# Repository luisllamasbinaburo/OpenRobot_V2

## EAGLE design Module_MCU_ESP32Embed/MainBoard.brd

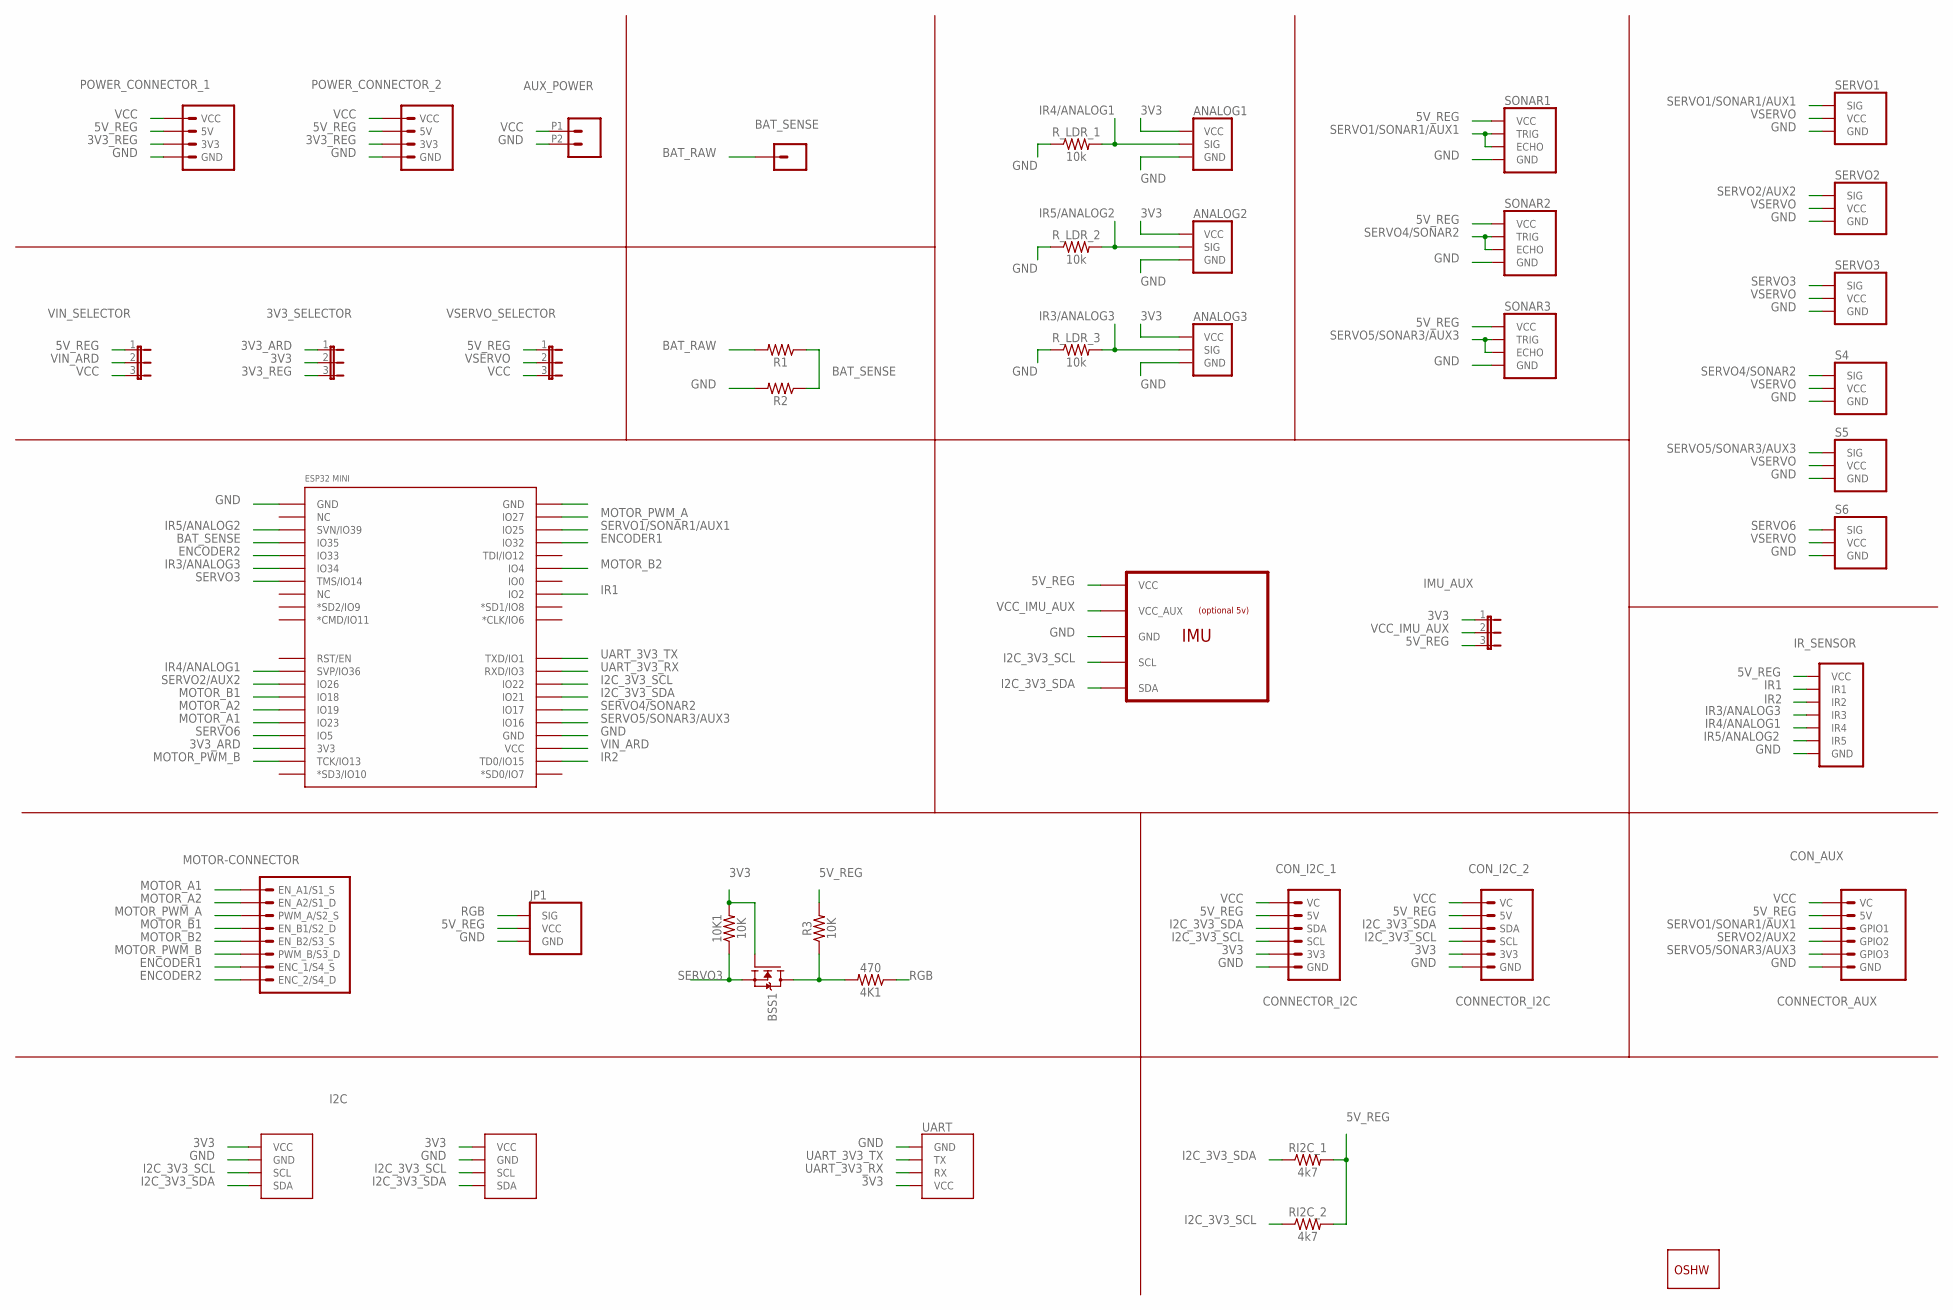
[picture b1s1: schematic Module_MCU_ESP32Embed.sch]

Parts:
3V3_SELECTOR: JUMPER_3
4K1: 470; 0805
10K1: 10K; 0805
ANALOG1, ANALOG2, ANALOG3: LDR/OCT; LDR
AUX_POWER: CONN_022.54MM_SCREWTERM; 1X02_2.54_SCREWTERM
BAT_SENSE: CONN_01; 1X01
BSS1: MOSFET-N-SOT23; SOT23
CON_AUX: CONNECTOR_AUX
CON_I2C_1, CON_I2C_2: CONNECTOR_I2C
GOLD_ORB_SM1: OSHWLOGO_GOLD_ORB_MED; OSHW1
I2C_1: I2C; I2C_VCC_GND_SCL_SDA
I2C_2: GENERIC_I2CVCC_GND_SCL_SDA; I2C_VCC_GND_SCL_SDA
IMU_AUX: JUMPER_3
IR_SENSOR: IR-5/OCT; IR-5
JP1: SERVOSERVO; SERVO
MOTOR_CONNECTOR: MOTOR-CONNECTOR
POWER_CONNECTOR_1, POWER_CONNECTOR_2: POWER-CONNECTOR
R1, R2: 1206
R3: 10K; 0805
RI2C_1, RI2C_2: 4k7; 1206
R_LDR_1, R_LDR_2, R_LDR_3: 10k; 1206
S4, S5, S6: SERVOSERVO; SERVO
SERVO1, SERVO2, SERVO3: SERVOSERVO; SERVO
SONAR1, SONAR2, SONAR3: ULTRASONIC/OCT; ULTRASONIC
U1: IMU_6/9/10DOFMPU6050; IMU_6/9/10DOF
U$5: ESP32-WEMOS
UART: UART; GENERIC_UART
VIN_SELECTOR: JUMPER_3
VSERVO_SELECTOR: JUMPER_3

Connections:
3V3_ARD: 3V3_SELECTOR.1, U$5.3V3
3V3_REG: 3V3_SELECTOR.3, POWER_CONNECTOR_1.3V3, POWER_CONNECTOR_2.3V3
BAT_RAW: BAT_SENSE.1, R1.2
BAT_SENSE: R1.1, R2.1, U$5.IO35
ENCODER1: MOTOR_CONNECTOR.ENC_1/S4_S, U$5.IO32
ENCODER2: MOTOR_CONNECTOR.ENC_2/S4_D, U$5.IO33
GND: ANALOG1.GND, ANALOG2.GND, ANALOG3.GND, AUX_POWER.P2 (2), CON_AUX.GND, CON_I2C_1.GND, CON_I2C_2.GND, I2C_1.GND, I2C_2.GND, IR_SENSOR.GND, JP1.GND, POWER_CONNECTOR_1.GND, POWER_CONNECTOR_2.GND, R2.2, R_LDR_1.1, R_LDR_2.1, R_LDR_3.1, S4.GND, S5.GND, S6.GND, SERVO1.GND, SERVO2.GND, SERVO3.GND, SONAR1.GND, SONAR2.GND, SONAR3.GND, U1.GND, U$5.GND@1 (GND), U$5.GND@3 (GND), UART.GND
I2C_3V3_SCL: CON_I2C_1.SCL, CON_I2C_2.SCL, I2C_1.SCL, I2C_2.SCL, RI2C_2.1, U1.SCL, U$5.IO22
I2C_3V3_SDA: CON_I2C_1.SDA, CON_I2C_2.SDA, I2C_1.SDA, I2C_2.SDA, RI2C_1.1, U1.SDA, U$5.IO21
IR1: IR_SENSOR.1 (IR1), U$5.IO2
IR2: IR_SENSOR.2 (IR2), U$5.TD0/IO15
IR3/ANALOG3: ANALOG3.SIG, IR_SENSOR.3 (IR3), R_LDR_3.2, U$5.IO34
IR4/ANALOG1: ANALOG1.SIG, IR_SENSOR.4 (IR4), R_LDR_1.2, U$5.SVP/IO36
IR5/ANALOG2: ANALOG2.SIG, IR_SENSOR.5 (IR5), R_LDR_2.2, U$5.SVN/IO39
MOTOR_A1: MOTOR_CONNECTOR.EN_A1/S1_S, U$5.IO23
MOTOR_A2: MOTOR_CONNECTOR.EN_A2/S1_D, U$5.IO19
MOTOR_B1: MOTOR_CONNECTOR.EN_B1/S2_D, U$5.IO18
MOTOR_B2: MOTOR_CONNECTOR.EN_B2/S3_S, U$5.IO4
MOTOR_PWM_A: MOTOR_CONNECTOR.PWM_A/S2_S, U$5.IO27
MOTOR_PWM_B: MOTOR_CONNECTOR.PWM_B/S3_D, U$5.TCK/IO13
unnamed: 4K1.2, BSS1.3 (D), R3.1
RGB: 4K1.1, JP1.SIG
SERVO1/SONAR1/AUX1: CON_AUX.GPIO1, SERVO1.SIG, SONAR1.ECHO, SONAR1.TRIG, U$5.IO25
SERVO2/AUX2: CON_AUX.GPIO2, SERVO2.SIG, U$5.IO26
SERVO3: 10K1.1, BSS1.2 (S), SERVO3.SIG, U$5.TMS/IO14
SERVO4/SONAR2: S4.SIG, SONAR2.ECHO, SONAR2.TRIG, U$5.IO17
SERVO5/SONAR3/AUX3: CON_AUX.GPIO3, S5.SIG, SONAR3.ECHO, SONAR3.TRIG, U$5.IO16
SERVO6: S6.SIG, U$5.IO5
UART_3V3_RX: U$5.RXD/IO3, UART.RX
UART_3V3_TX: U$5.TXD/IO1, UART.TX
VCC: AUX_POWER.P1 (1), CON_AUX.VC, CON_I2C_1.VC, CON_I2C_2.VC, POWER_CONNECTOR_1.VCC, POWER_CONNECTOR_2.VCC, VIN_SELECTOR.3, VSERVO_SELECTOR.3
VCC_IMU_AUX: IMU_AUX.2, U1.VCC_AUX
VIN_ARD: U$5.VCC, VIN_SELECTOR.2
VSERVO: S4.VCC, S5.VCC, S6.VCC, SERVO1.VCC, SERVO2.VCC, SERVO3.VCC, VSERVO_SELECTOR.2

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
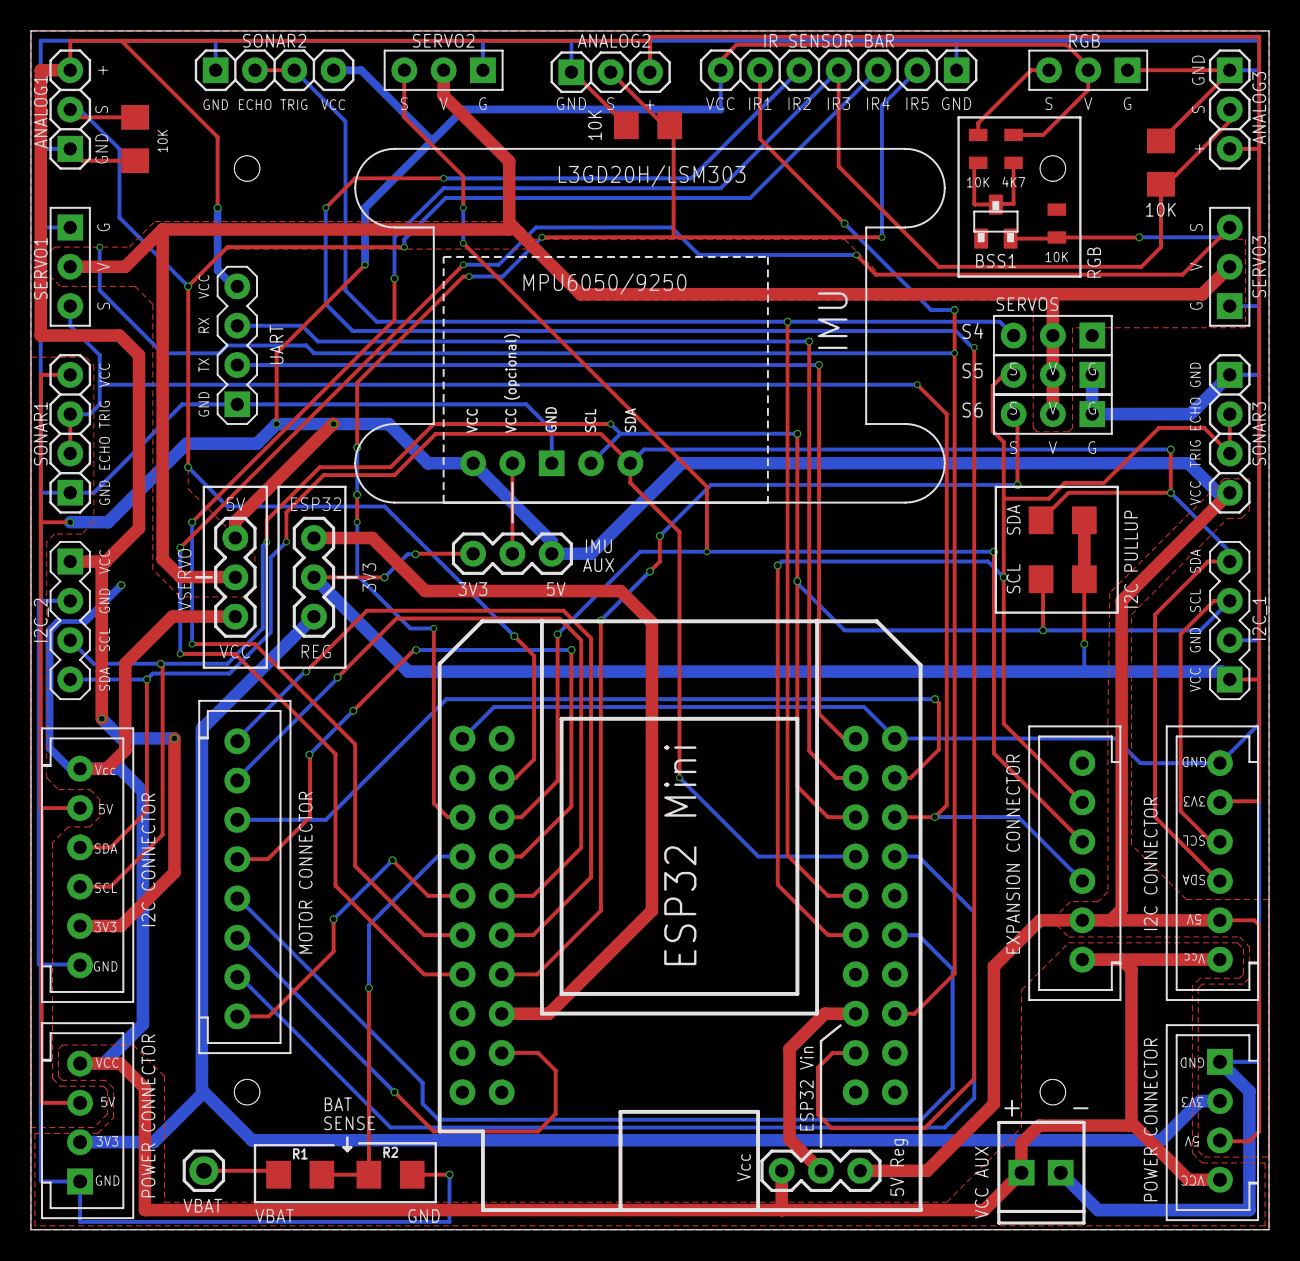
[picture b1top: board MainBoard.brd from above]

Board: 2 copper layers, 80.0 x 77.5 mm, 43 parts (1 on the bottom side), 36 nets.

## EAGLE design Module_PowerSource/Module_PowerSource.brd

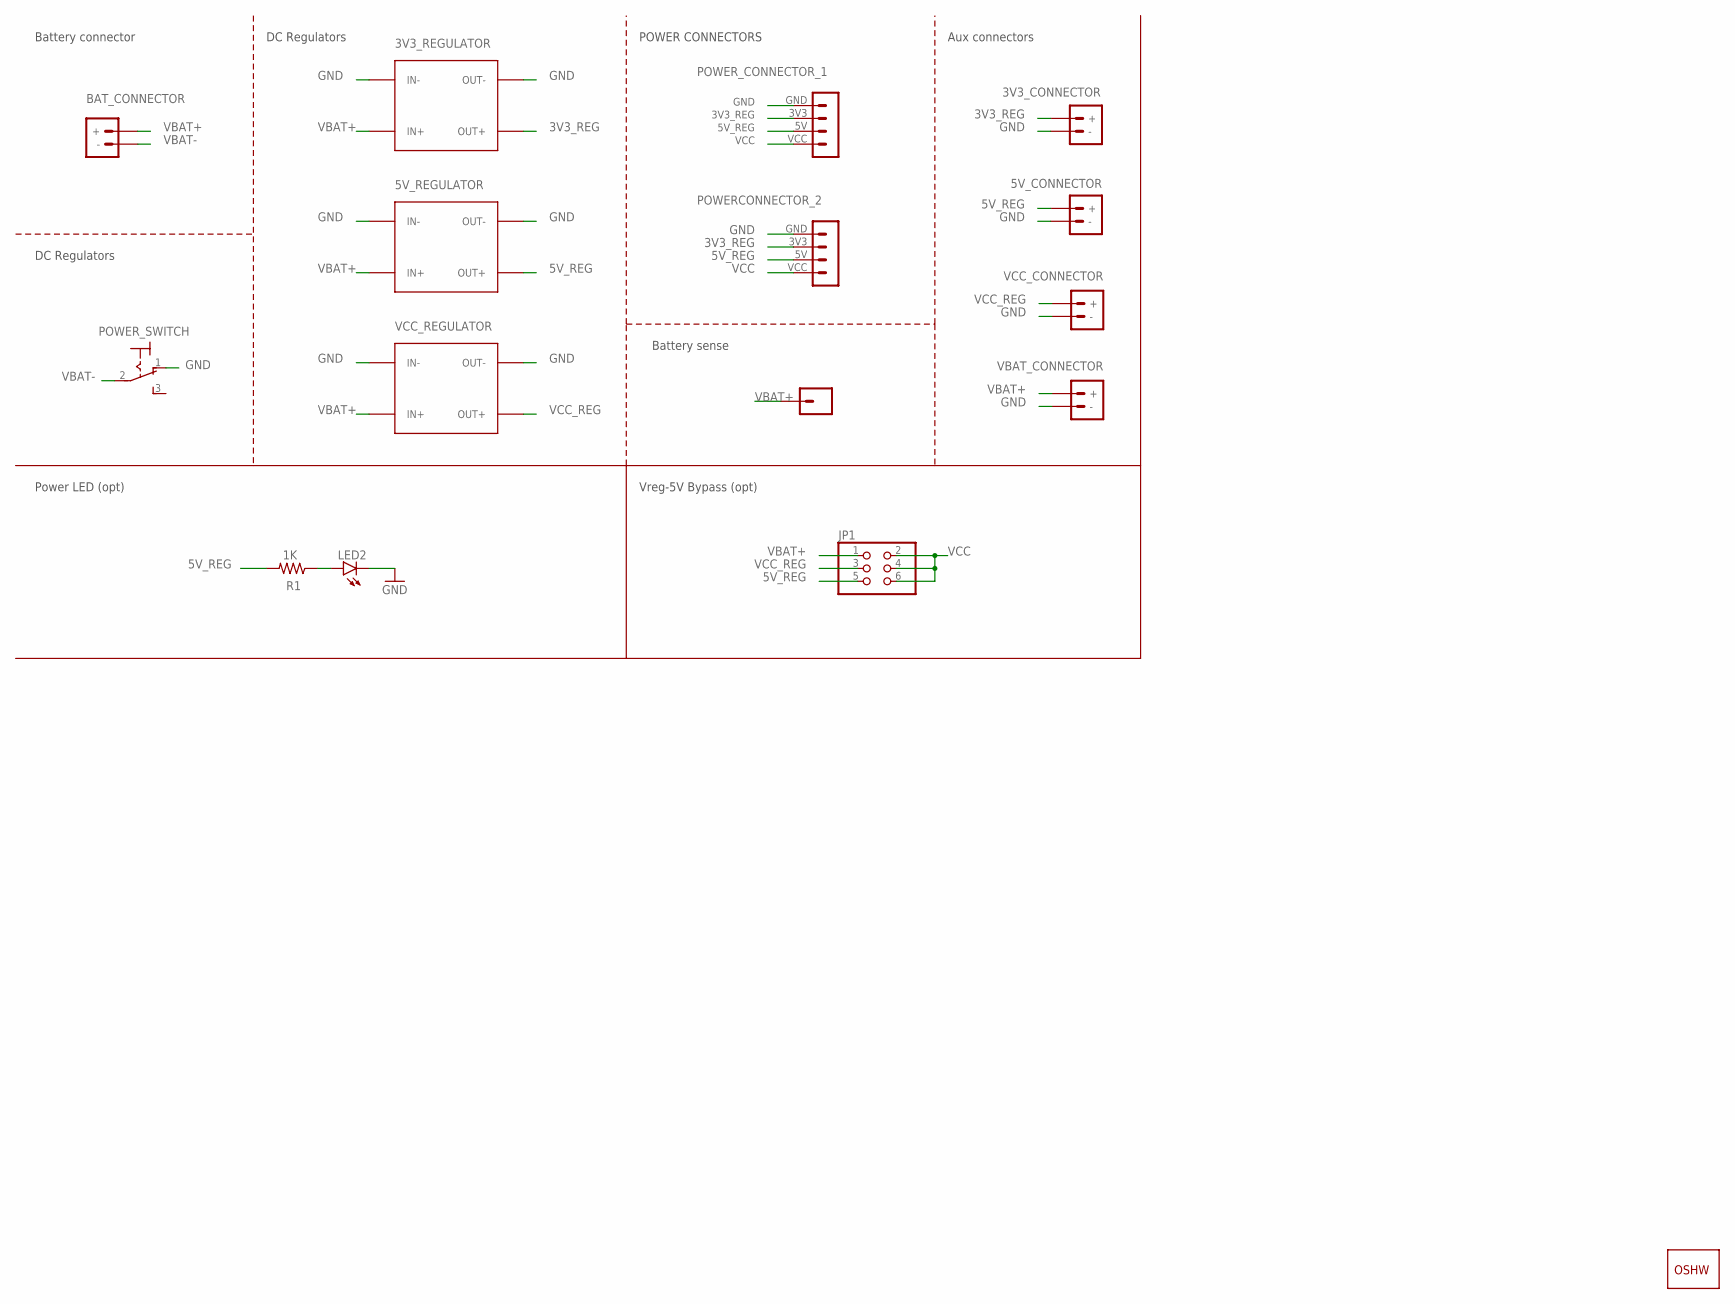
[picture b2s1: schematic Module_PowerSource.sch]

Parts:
3V3_CONNECTOR, 5V_CONNECTOR: MOTOR-TERMINAL2.54MM_SCREWTERM; 1X02_2.54_SCREWTERM
3V3_REGULATOR, 5V_REGULATOR: MINI-DC-STEP-DOWN-MP2307
BAT_CONNECTOR: POWER-TERMINAL5MM; SCREWTERMINAL-5MM-2
GOLD_ORB_SM1: OSHWLOGO_GOLD_ORB_MED; OSHW1
J3: CONN_01; 1X01
JP1: JUMPER_3X2/OCT; JUMPER_3X2
LED2: LEDCHIP-LED0805; CHIP-LED0805
POWERCONNECTOR_2: POWER-CONNECTOR
POWER_CONNECTOR_1: POWER-CONNECTOR
POWER_SWITCH: LEVER-POWER-SWITCH
R1: 1K; R0805
VBAT_CONNECTOR: MOTOR-TERMINAL2.54MM_SCREWTERM; 1X02_2.54_SCREWTERM
VCC_CONNECTOR: MOTOR-TERMINAL2.54MM_SCREWTERM; 1X02_2.54_SCREWTERM
VCC_REGULATOR: MINI-DC-STEP-DOWN-MP2307

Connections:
3V3_REG: 3V3_CONNECTOR.+, 3V3_REGULATOR.OUT2.+ (OUT+), 3V3_REGULATOR.OUT+, POWERCONNECTOR_2.3V3, POWER_CONNECTOR_1.3V3
5V_REG: 5V_CONNECTOR.+, 5V_REGULATOR.OUT2.+ (OUT+), 5V_REGULATOR.OUT+, JP1.5, POWERCONNECTOR_2.5V, POWER_CONNECTOR_1.5V, R1.2
GND: 3V3_CONNECTOR.-, 3V3_REGULATOR.IN-, 3V3_REGULATOR.OUT-, 5V_CONNECTOR.-, 5V_REGULATOR.IN-, 5V_REGULATOR.OUT-, LED2.C, POWERCONNECTOR_2.GND, POWER_CONNECTOR_1.GND, POWER_SWITCH.1 (O), VBAT_CONNECTOR.-, VCC_CONNECTOR.-, VCC_REGULATOR.IN-, VCC_REGULATOR.OUT-
unnamed: LED2.A, R1.1
VBAT+: 3V3_REGULATOR.IN+, 3V3_REGULATOR.IN.2+ (IN+), 5V_REGULATOR.IN+, 5V_REGULATOR.IN.2+ (IN+), BAT_CONNECTOR.+, J3.1, JP1.1, VBAT_CONNECTOR.+, VCC_REGULATOR.IN+, VCC_REGULATOR.IN.2+ (IN+)
VBAT-: BAT_CONNECTOR.-, POWER_SWITCH.2
VCC: JP1.2, JP1.4, JP1.6, POWERCONNECTOR_2.VCC, POWER_CONNECTOR_1.VCC
VCC_REG: JP1.3, VCC_CONNECTOR.+, VCC_REGULATOR.OUT2.+ (OUT+), VCC_REGULATOR.OUT+

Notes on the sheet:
Aux connectors
Battery sense
DC Regulators
Battery connector
Power LED (opt)
Vreg-5V Bypass (opt)
POWER CONNECTORS

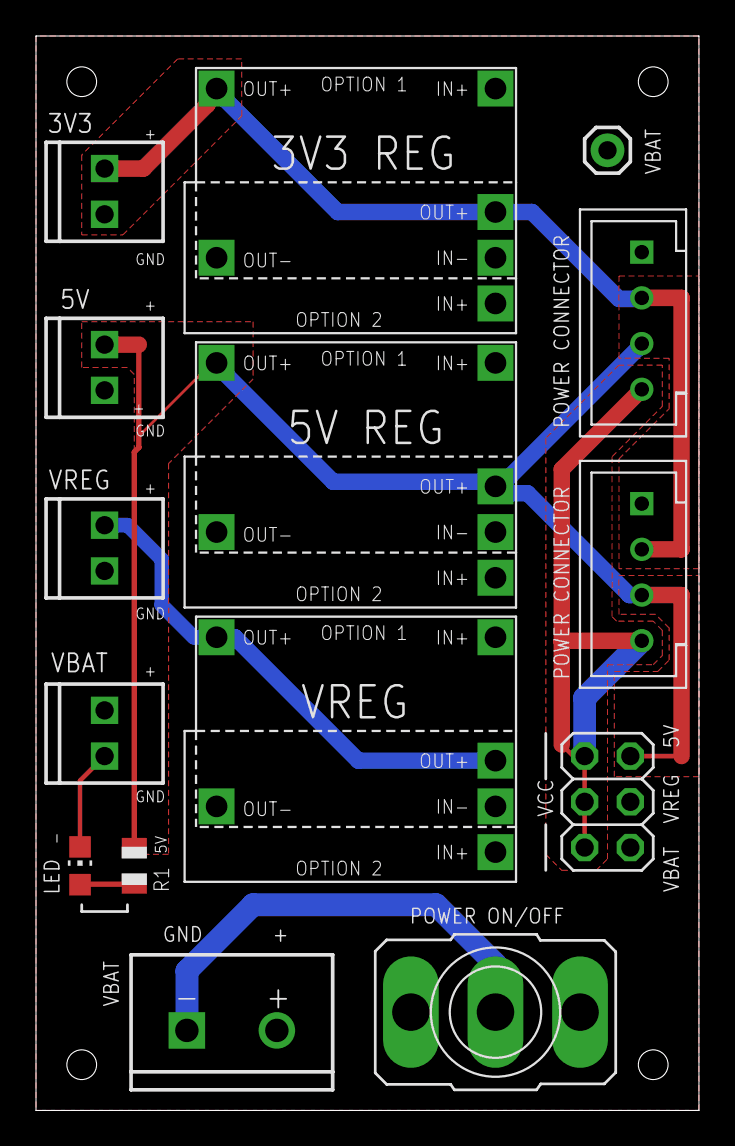
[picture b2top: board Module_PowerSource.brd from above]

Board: 2 copper layers, 36.8 x 59.7 mm, 16 parts (1 on the bottom side), 8 nets.

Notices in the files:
parts and their libraries:
SparkFun-Resistors: Licensing: Creative Commons ShareAlike 4.0 International - https://creativecommons.org/licenses/by-sa/4.0
